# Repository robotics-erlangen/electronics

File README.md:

# Robotics Erlangen e.V. &ndash; Open Source SSL Robot Hardware
Raw and compiled files for the open source hardware of the German SSL team ER-Force.

## Commit Structure
Commits that have been tagged represent a self-contained robot state,
i.e. the PCB's and mechanical components work well with each other.

## Folder Structure
At the top level of the repository, there is a separate folder for each robot generation.
Currently, only parts of our latest robot generation 'pasta' have been published.
Each robot generation is divided into two sections: mechanics and electronics.

The electronics section has the following structure:
- boards: Contains a separate folder for each PCB that is part of the robot
- eagle: Contains generic libraries, design rule files, etc.

Within each PCB's folder, there are multiple subfolders:
- documents: A pdf version of the schematics as well as optional documentation
- eagle: The schematics and layout in the raw EAGLE file format, i.e.
  - the schematics (*.sch)
  - the layout (*.brd)
  - a library with all board-specific, non-generic components (*.lbr)
  - the design rule file used (*.dru)
  - the cam job used to generate the gerber files (*.cam)
- gerber: The compiled layout files, i.e.
  - the Gerber files
  - the Excellon drill files
  - the Pick & Place files for the top and bottom side
  - a bill of materials

## Example
- ```/pasta```: all files related to the 'pasta' generation
- ```/pasta/electronics```: electronic files for the 'pasta' generation
- ```/pasta/electronics/eagle```: generic eagle files usable accross multiple 'pasta' PCBs
- ```/pasta/electronics/boards```: all PCBs used in the 'pasta' generation
- ```/pasta/electronics/boards/kicker```: all data related to the kicker board of the 'pasta' generation
- ```/pasta/electronics/boards/kicker/eagle```: the raw eagle data of the kicker board
- ```/pasta/electronics/boards/kicker/gerber```: the compiled files of the kicker board
- ```/pasta/electronics/boards/kicker/documents```: additional documentation for the kicker board (e.g. schematics as pdf)

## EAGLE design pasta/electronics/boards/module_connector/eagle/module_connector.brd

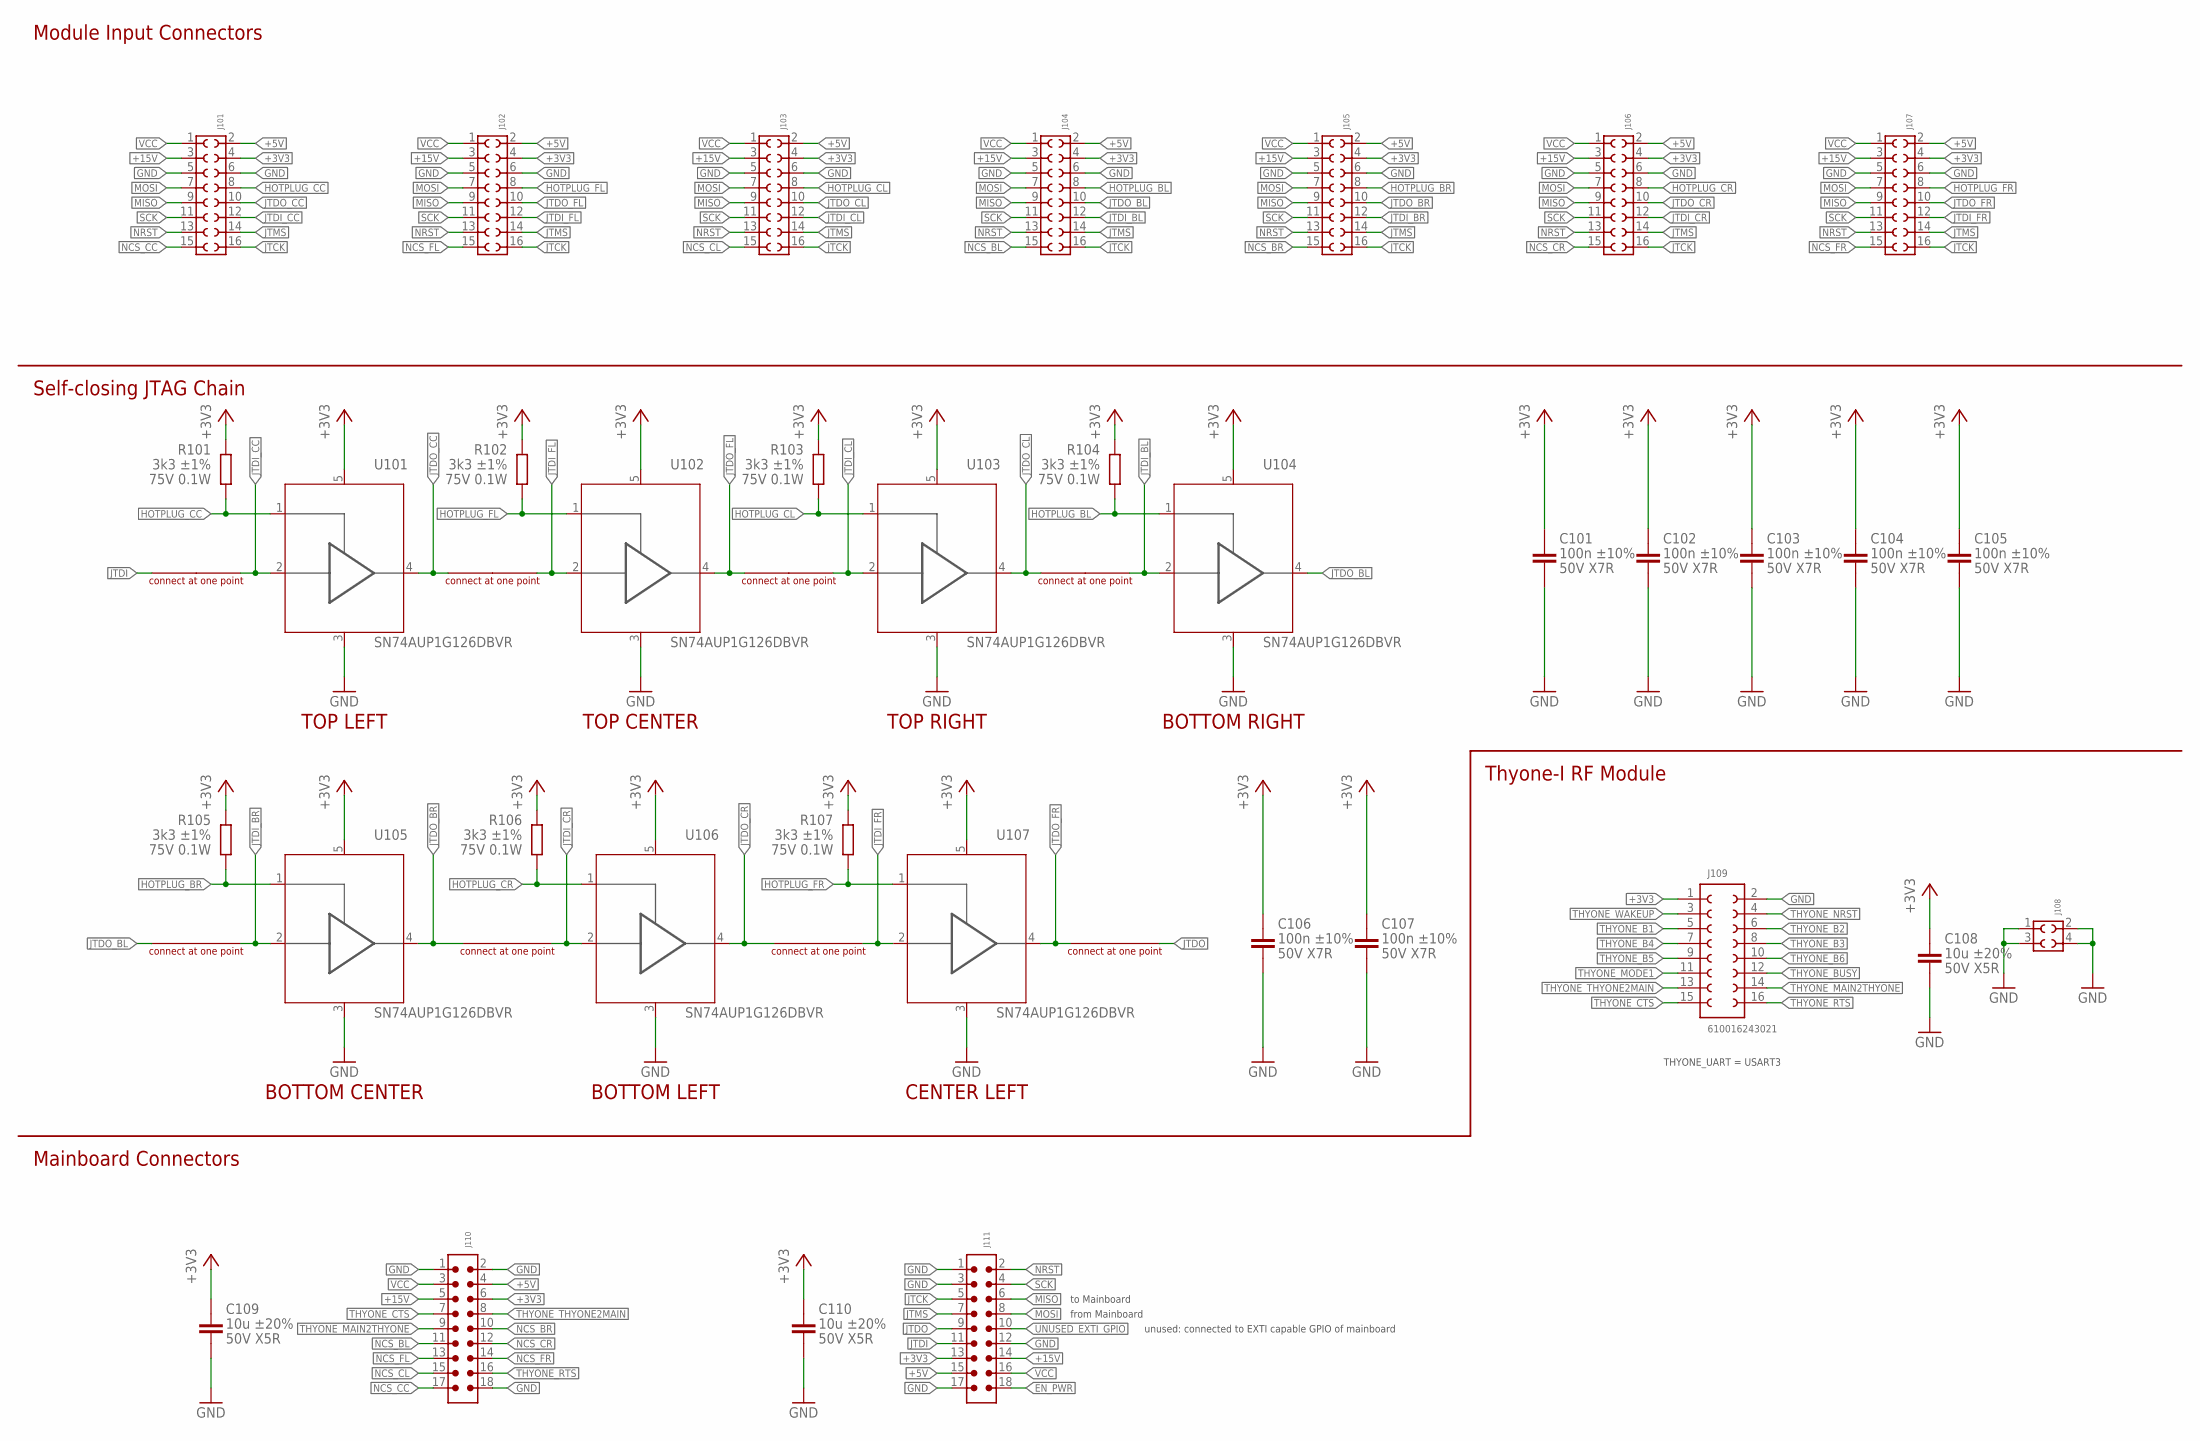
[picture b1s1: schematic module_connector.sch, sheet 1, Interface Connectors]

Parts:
C101, C102, C103, C104, C105, C106, C107: 100n ±10% 50V X7R; C0603
C108, C109, C110: 10u ±20% 50V X5R; C1206
J101, J102, J103, J104, J105, J106, J107: 6100XX243021_610016243021; 610016243021
J108: 6100XX243021_610004243021; 610004243021
J109: 610016243021; 610X16243021
J110, J111: 6130XX21121_61301821121; 61301821121
R101, R102, R103, R104, R105, R106, R107: 3k3 ±1% 75V 0.1W; R0603
SHORT101, SHORT102, SHORT103, SHORT104, SHORT105, SHORT106, SHORT107, SHORT108: SHORT0.254
U101, U102, U103, U104, U105, U106, U107: SN74AUP1G126DBVR; SOT23-5

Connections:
+3V3: C101.1, C102.1, C103.1, C104.1, C105.1, C106.1, C107.1, C108.1, C109.1, C110.1, J101.4, J102.4, J103.4, J104.4, J105.4, J106.4, J107.4, J109.1, J110.6, J111.13, R101.2, R102.2, R103.2, R104.2, R105.2, R106.2, R107.2, U101.5 (VCC), U102.5 (VCC), U103.5 (VCC), U104.5 (VCC), U105.5 (VCC), U106.5 (VCC), U107.5 (VCC)
+5V: J101.2, J102.2, J103.2, J104.2, J105.2, J106.2, J107.2, J110.4, J111.15
+15V: J101.3, J102.3, J103.3, J104.3, J105.3, J106.3, J107.3, J110.5, J111.14
EN_PWR: J111.18
GND: C101.2, C102.2, C103.2, C104.2, C105.2, C106.2, C107.2, C108.2, C109.2, C110.2, J101.5, J101.6, J102.5, J102.6, J103.5, J103.6, J104.5, J104.6, J105.5, J105.6, J106.5, J106.6, J107.5, J107.6, J108.1, J108.2, J108.3, J108.4, J109.2 (16), J110.1, J110.2, J110.18, J111.1, J111.3, J111.12, J111.17, U101.3 (GND), U102.3 (GND), U103.3 (GND), U104.3 (GND), U105.3 (GND), U106.3 (GND), U107.3 (GND)
HOTPLUG_BL: J104.8, R104.1, U104.1 (OE)
HOTPLUG_BR: J105.8, R105.1, U105.1 (OE)
HOTPLUG_CC: J101.8, R101.1, U101.1 (OE)
HOTPLUG_CL: J103.8, R103.1, U103.1 (OE)
HOTPLUG_CR: J106.8, R106.1, U106.1 (OE)
HOTPLUG_FL: J102.8, R102.1, U102.1 (OE)
HOTPLUG_FR: J107.8, R107.1, U107.1 (OE)
JTCK: J101.16, J102.16, J103.16, J104.16, J105.16, J106.16, J107.16, J111.5
JTDI: J111.11, SHORT101.P1
JTDI_BL: J104.12, SHORT104.P2, U104.2 (I)
JTDI_BR: J105.12, SHORT105.P2, U105.2 (I)
JTDI_CC: J101.12, SHORT101.P2, U101.2 (I)
JTDI_CL: J103.12, SHORT103.P2, U103.2 (I)
JTDI_CR: J106.12, SHORT106.P2, U106.2 (I)
JTDI_FL: J102.12, SHORT102.P2, U102.2 (I)
JTDI_FR: J107.12, SHORT107.P2, U107.2 (I)
JTDO: J111.9, SHORT108.P2
JTDO_BL: J104.10, SHORT105.P1, U104.4 (O)
JTDO_BR: J105.10, SHORT106.P1, U105.4 (O)
JTDO_CC: J101.10, SHORT102.P1, U101.4 (O)
JTDO_CL: J103.10, SHORT104.P1, U103.4 (O)
JTDO_CR: J106.10, SHORT107.P1, U106.4 (O)
JTDO_FL: J102.10, SHORT103.P1, U102.4 (O)
JTDO_FR: J107.10, SHORT108.P1, U107.4 (O)
JTMS: J101.14, J102.14, J103.14, J104.14, J105.14, J106.14, J107.14, J111.7
MISO: J101.9, J102.9, J103.9, J104.9, J105.9, J106.9, J107.9, J111.6
MOSI: J101.7, J102.7, J103.7, J104.7, J105.7, J106.7, J107.7, J111.8
NCS_BL: J104.15, J110.11
NCS_BR: J105.15, J110.10
NCS_CC: J101.15, J110.17
NCS_CL: J103.15, J110.15
NCS_CR: J106.15, J110.12
NCS_FL: J102.15, J110.13
NCS_FR: J107.15, J110.14
NRST: J101.13, J102.13, J103.13, J104.13, J105.13, J106.13, J107.13, J111.2
SCK: J101.11, J102.11, J103.11, J104.11, J105.11, J106.11, J107.11, J111.4
THYONE_B1: J109.5 (3)
THYONE_B2: J109.6 (14)
THYONE_B3: J109.8 (13)
THYONE_B4: J109.7 (4)
THYONE_B5: J109.9 (5)
THYONE_B6: J109.10 (12)
THYONE_BUSY: J109.12 (11)
THYONE_CTS: J109.15 (8), J110.7
THYONE_MAIN2THYONE: J109.14 (10), J110.9
THYONE_MODE1: J109.11 (6)
THYONE_NRST: J109.4 (15)
THYONE_RTS: J109.16 (9), J110.16
THYONE_THYONE2MAIN: J109.13 (7), J110.8
THYONE_WAKEUP: J109.3 (2)
UNUSED_EXTI_GPIO: J111.10
VCC: J101.1, J102.1, J103.1, J104.1, J105.1, J106.1, J107.1, J110.3, J111.16

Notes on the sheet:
Module Input Connectors
Self-closing JTAG Chain
TOP LEFT
TOP CENTER
TOP RIGHT
BOTTOM RIGHT
BOTTOM CENTER
BOTTOM LEFT
CENTER LEFT
Mainboard Connectors
Thyone-I RF Module
from Mainboard
to Mainboard
THYONE_UART = USART3
unused: connected to EXTI capable GPIO of mainboard

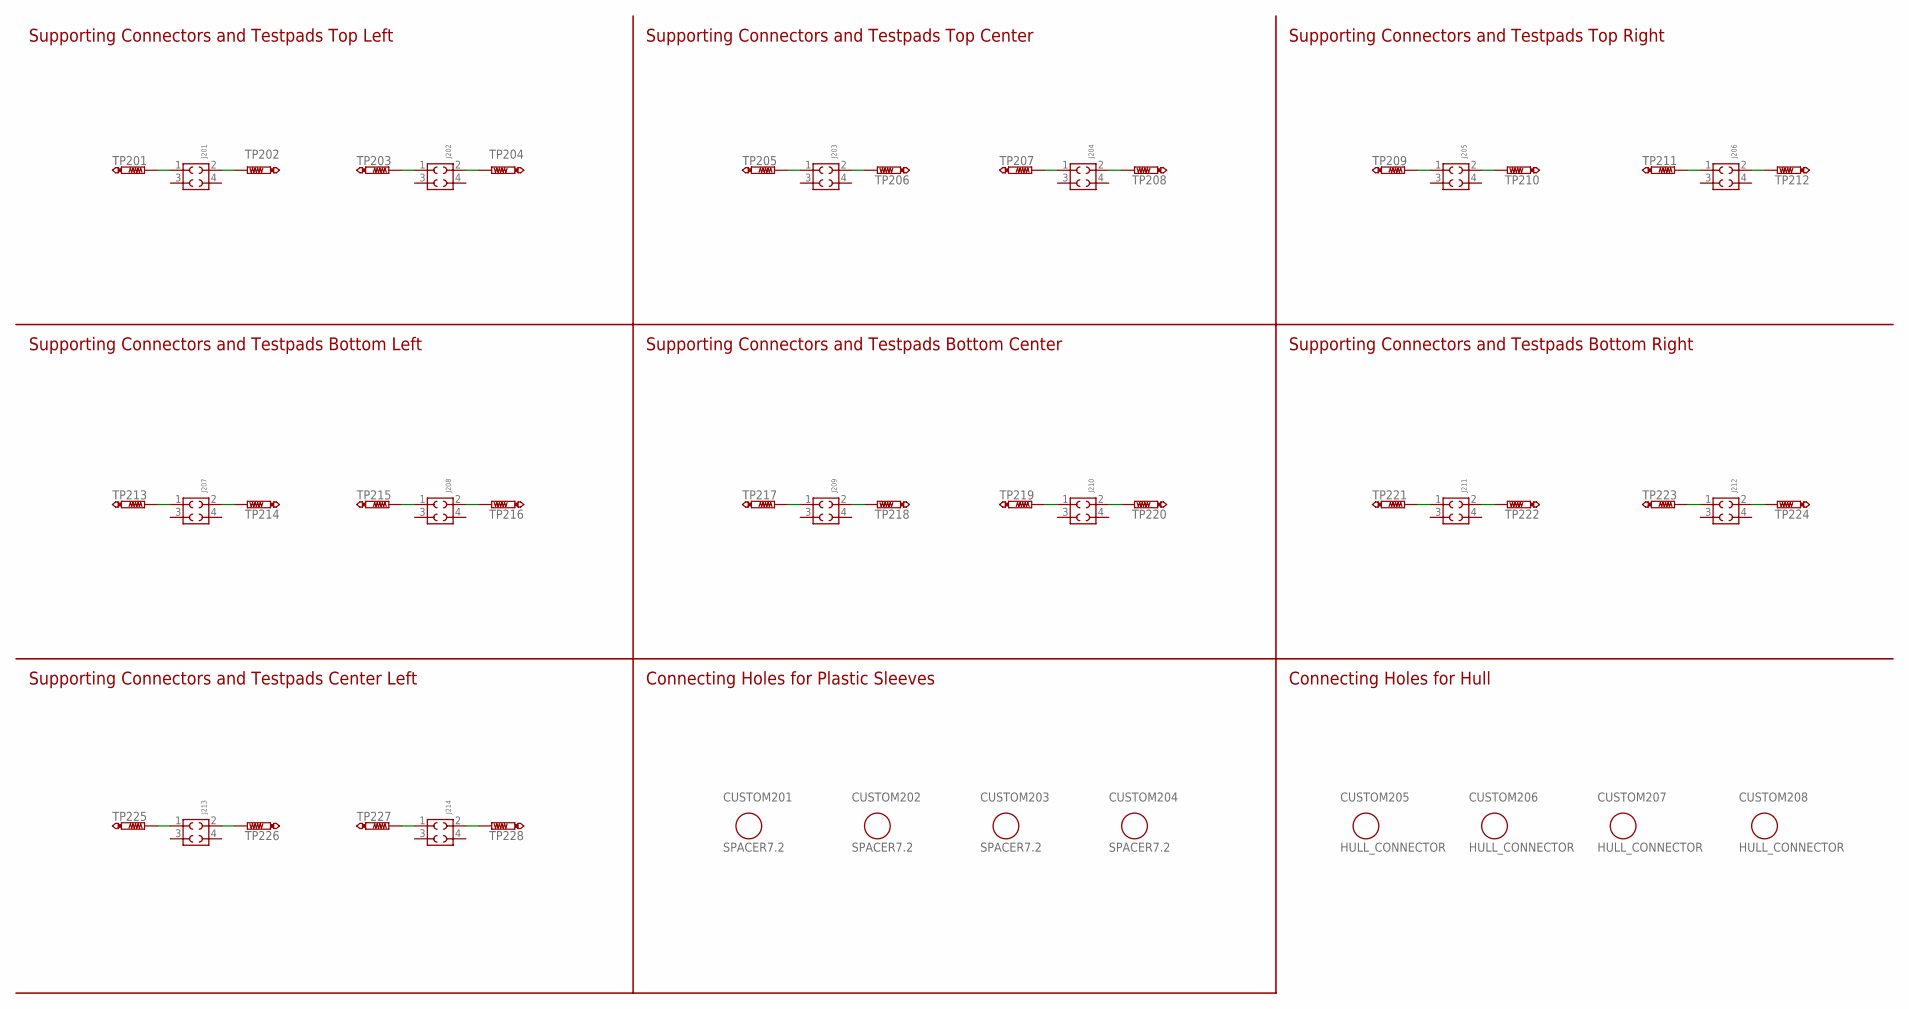
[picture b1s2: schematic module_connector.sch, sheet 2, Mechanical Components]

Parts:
CUSTOM201, CUSTOM202, CUSTOM203, CUSTOM204: SPACER7.2; PLASTIC_SPACER
CUSTOM205, CUSTOM206, CUSTOM207, CUSTOM208: HULL_CONNECTOR
J201, J202, J203, J204, J205, J206, J207, J208, J209, J210, J211, J212, J213, J214: 6100XX243021_610004243021; 610004243021
TP201, TP202, TP203, TP204, TP205, TP206, TP207, TP208, TP209, TP210, TP211, TP212, TP213, TP214, TP215, TP216, TP217, TP218, TP219, TP220, TP221, TP222, TP223, TP224, TP225, TP226, TP227, TP228: TESTPAD

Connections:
unnamed: J201.1, TP201.P$1
unnamed: J201.2, TP202.P$1
unnamed: J203.1, TP205.P$1
unnamed: J203.2, TP206.P$1
unnamed: J202.1, TP203.P$1
unnamed: J204.1, TP207.P$1
unnamed: J202.2, TP204.P$1
unnamed: J204.2, TP208.P$1
unnamed: J205.1, TP209.P$1
unnamed: J205.2, TP210.P$1
unnamed: J206.1, TP211.P$1
unnamed: J206.2, TP212.P$1
unnamed: J207.1, TP213.P$1
unnamed: J207.2, TP214.P$1
unnamed: J208.1, TP215.P$1
unnamed: J208.2, TP216.P$1
unnamed: J209.1, TP217.P$1
unnamed: J209.2, TP218.P$1
unnamed: J210.1, TP219.P$1
unnamed: J210.2, TP220.P$1
unnamed: J211.1, TP221.P$1
unnamed: J211.2, TP222.P$1
unnamed: J212.1, TP223.P$1
unnamed: J212.2, TP224.P$1
unnamed: J213.1, TP225.P$1
unnamed: J213.2, TP226.P$1
unnamed: J214.1, TP227.P$1
unnamed: J214.2, TP228.P$1

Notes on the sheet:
Supporting Connectors and Testpads Top Left
Supporting Connectors and Testpads Top Center
Supporting Connectors and Testpads Top Right
Supporting Connectors and Testpads Bottom Left
Supporting Connectors and Testpads Bottom Center
Supporting Connectors and Testpads Bottom Right
Supporting Connectors and Testpads Center Left
Connecting Holes for Plastic Sleeves
Connecting Holes for Hull

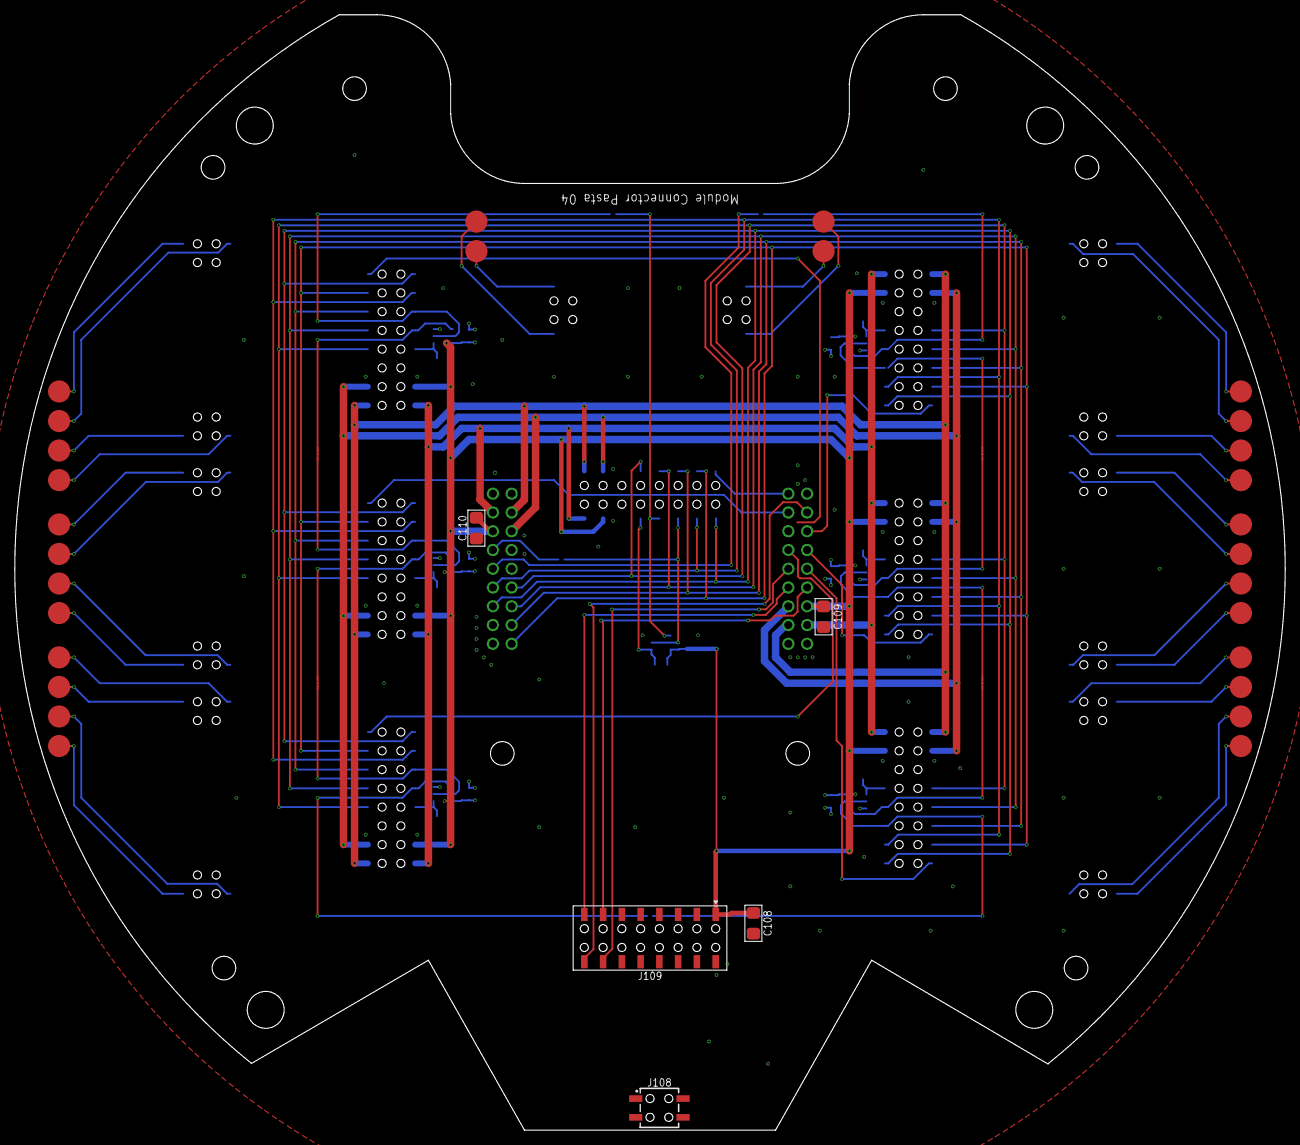
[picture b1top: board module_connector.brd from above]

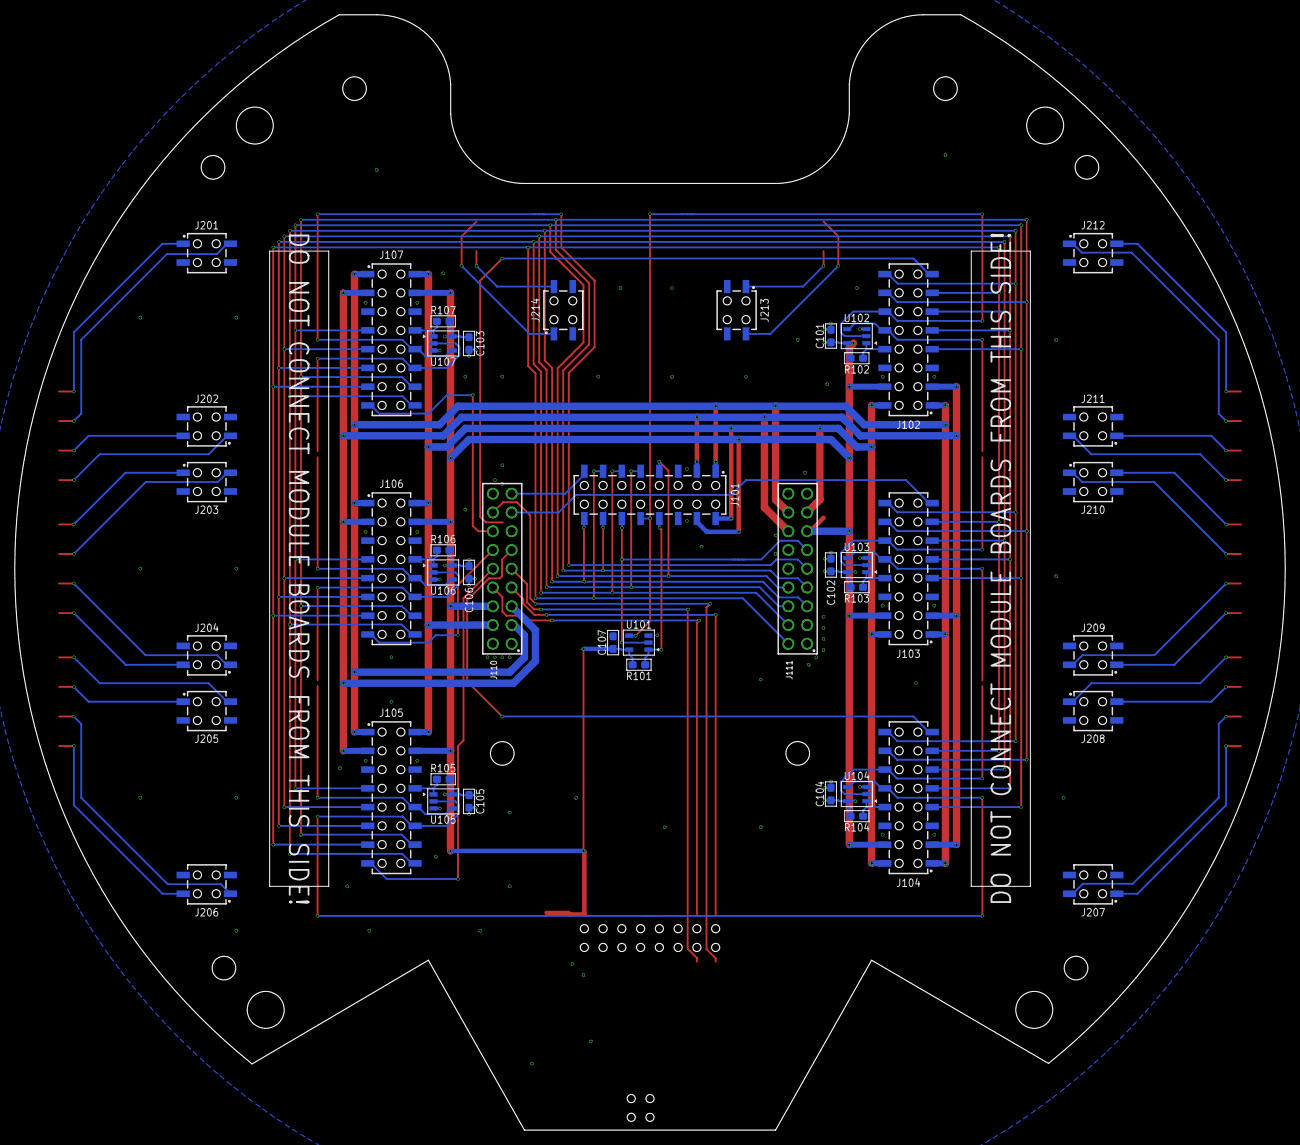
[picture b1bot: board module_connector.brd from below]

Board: 2 copper layers, 172.0 x 151.0 mm, 104 parts (48 on the bottom side), 73 nets.

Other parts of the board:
U$1, U$13, U$15, U$20, U$21, U$22, U$23: MODULE_BOARD
U$2: HULL
U$3: RF-MODULE
U$16, U$17: LOGO

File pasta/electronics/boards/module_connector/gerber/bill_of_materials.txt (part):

Stückliste exportiert aus D:/hardware/pasta/electronics/boards/module_connector/eagle/module_connector.sch am 04.07.2023 15:54

Part      Value             Device                    Package        Description                                         CAPACITANCE DIELECTRIC LINE1     LINE2    MF                MOUSER               MPN              POWER RESISTANCE TOLERANCE VALUE             VOLTAGE
C101      100n ±10% 50V X7R C(100NF,50V,0603)         C0603          Robotics Erlangen Capacitor Library                 100n        X7R        100n ±10% 50V X7R  Würth Elektronik                       885012206095                      ±10%      100n ±10% 50V X7R 50V    
C102      100n ±10% 50V X7R C(100NF,50V,0603)         C0603          Robotics Erlangen Capacitor Library                 100n        X7R        100n ±10% 50V X7R  Würth Elektronik                       885012206095                      ±10%      100n ±10% 50V X7R 50V    
C103      100n ±10% 50V X7R C(100NF,50V,0603)         C0603          Robotics Erlangen Capacitor Library                 100n        X7R        100n ±10% 50V X7R  Würth Elektronik                       885012206095                      ±10%      100n ±10% 50V X7R 50V    
C104      100n ±10% 50V X7R C(100NF,50V,0603)         C0603          Robotics Erlangen Capacitor Library                 100n        X7R        100n ±10% 50V X7R  Würth Elektronik                       885012206095                      ±10%      100n ±10% 50V X7R 50V    
C105      100n ±10% 50V X7R C(100NF,50V,0603)         C0603          Robotics Erlangen Capacitor Library                 100n        X7R        100n ±10% 50V X7R  Würth Elektronik                       885012206095                      ±10%      100n ±10% 50V X7R 50V    
C106      100n ±10% 50V X7R C(100NF,50V,0603)         C0603          Robotics Erlangen Capacitor Library                 100n        X7R        100n ±10% 50V X7R  Würth Elektronik                       885012206095                      ±10%      100n ±10% 50V X7R 50V    
C107      100n ±10% 50V X7R C(100NF,50V,0603)         C0603          Robotics Erlangen Capacitor Library                 100n        X7R        100n ±10% 50V X7R  Würth Elektronik                       885012206095                      ±10%      100n ±10% 50V X7R 50V    
C108      10u ±20% 50V X5R  C(10UF,50V,1206)          C1206          Robotics Erlangen Capacitor Library                 10u         X5R        10u ±20%  50V X5R  Samsung                                CL31A106MBHNNNE                   ±20%      10u ±20% 50V X5R  50V    
C109      10u ±20% 50V X5R  C(10UF,50V,1206)          C1206          Robotics Erlangen Capacitor Library                 10u         X5R        10u ±20%  50V X5R  Samsung                                CL31A106MBHNNNE                   ±20%      10u ±20% 50V X5R  50V    
C110      10u ±20% 50V X5R  C(10UF,50V,1206)          C1206          Robotics Erlangen Capacitor Library                 10u         X5R        10u ±20%  50V X5R  Samsung                                CL31A106MBHNNNE                   ±20%      10u ±20% 50V X5R  50V    
CUSTOM201 SPACER7.2         SPACER7.2                 PLASTIC_SPACER                                                                                                                                                                                                           
CUSTOM202 SPACER7.2         SPACER7.2                 PLASTIC_SPACER                                                                                                                                                                                                           
CUSTOM203 SPACER7.2         SPACER7.2                 PLASTIC_SPACER                                                                                                                                                                                                           
CUSTOM204 SPACER7.2         SPACER7.2                 PLASTIC_SPACER                                                                                                                                                                                                           
CUSTOM205 HULL_CONNECTOR    HULL_CONNECTOR            HULL_CONNECTOR                                                                                                                                                                                                           
CUSTOM206 HULL_CONNECTOR    HULL_CONNECTOR            HULL_CONNECTOR                                                                                                                                                                                                           
CUSTOM207 HULL_CONNECTOR    HULL_CONNECTOR            HULL_CONNECTOR                                                                                                                                                                                                           
CUSTOM208 HULL_CONNECTOR    HULL_CONNECTOR            HULL_CONNECTOR                                                                                                                                                                                                           
J101                        6100XX243021_610016243021 610016243021   WR-PHD 2.54 mm SMT Dual Socket Header Bottom Entry                                            Würth Elektronik                       610016243021                                                         
J102                        6100XX243021_610016243021 610016243021   WR-PHD 2.54 mm SMT Dual Socket Header Bottom Entry                                            Würth Elektronik                       610016243021                                                         
J103                        6100XX243021_610016243021 610016243021   WR-PHD 2.54 mm SMT Dual Socket Header Bottom Entry                                            Würth Elektronik                       610016243021                                                         
J104                        6100XX243021_610016243021 610016243021   WR-PHD 2.54 mm SMT Dual Socket Header Bottom Entry                                            Würth Elektronik                       610016243021                                                         
J105                        6100XX243021_610016243021 610016243021   WR-PHD 2.54 mm SMT Dual Socket Header Bottom Entry                                            Würth Elektronik                       610016243021                                                         
J106                        6100XX243021_610016243021 610016243021   WR-PHD 2.54 mm SMT Dual Socket Header Bottom Entry                                            Würth Elektronik                       610016243021                                                         
J107                        6100XX243021_610016243021 610016243021   WR-PHD 2.54 mm SMT Dual Socket Header Bottom Entry                                            Würth Elektronik                       610016243021                                                         
J108                        6100XX243021_610004243021 610004243021   WR-PHD 2.54 mm SMT Dual Socket Header Bottom Entry                                            Würth Elektronik                       610004243021                                                         
J109      610016243021      610016243021              610X16243021   16-Pin Bottom Entry Connector from Würth Elektronik                                           Würth Elektronik                       610016243021                                                         
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

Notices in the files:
parts and their libraries:
COPYRIGHT: Copyright (C) 2021 Ultra Librarian. All rights reserved.
COPYRIGHT: Copyright (C) 2022 Ultra Librarian. All rights reserved.
